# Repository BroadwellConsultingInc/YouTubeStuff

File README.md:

# YouTubeStuff
Materials Related to various YouTube Videos

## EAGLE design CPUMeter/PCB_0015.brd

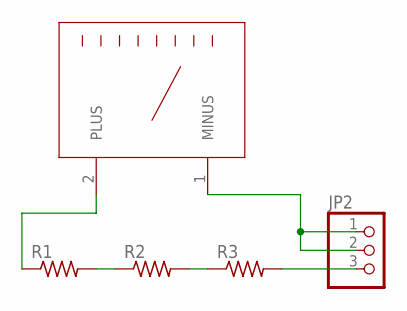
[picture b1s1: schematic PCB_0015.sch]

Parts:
JP2: PINHD-1X3; 1X03
R1, R2, R3: R-US_R0603; R0603
U$1: METER; METER_85C1

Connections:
unnamed: JP2.1, JP2.2, U$1.1 (MINUS)
unnamed: R1.1, U$1.2 (PLUS)
unnamed: JP2.3, R3.2
unnamed: R2.2, R3.1
unnamed: R1.2, R2.1

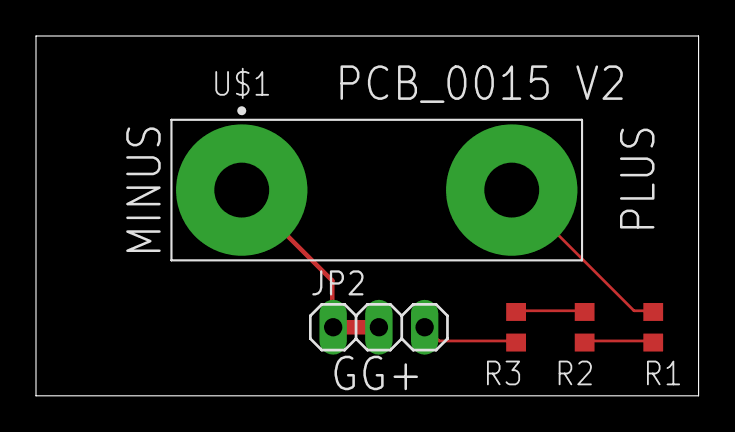
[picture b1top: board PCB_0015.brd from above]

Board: 2 copper layers, 36.8 x 20.0 mm, 5 parts (0 on the bottom side), 5 nets.

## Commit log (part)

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2022-12-28 Adding information for YouTube Video https://youtu.be/LtUx8s8pZ1c
2023-07-24 Adding ScreenBroadcast
2023-07-24 adding readme
2023-07-30 Laser Cut Vial Holder
2024-11-06 Adding Video support material
2024-12-18 Adding files for videos
2025-02-24 Adding PID examples
2025-03-01 Adding Railroad Crossing
2026-01-31 LVGL CYD Demo
2026-05-24 Adding Serial Wombat DM8A10 YouTube Demo
